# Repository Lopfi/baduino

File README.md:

# baduino
This is baduino!
An open source bad usb based on the Atmega 32u4. It is inspired by and uses the firmware from Seytonics Malduino Elite. 
It can store up to 16 different scripts on it's SD card, each of which can be selected on the fly with 4 dip switches.

# Firmware and bootloader
Get the firmware and arduino config from the malduino repository: [https://github.com/Seytonic/malduino](https://github.com/Seytonic/malduino)

# TODO
- Make PCB a bit nicer
- Create BOM
- Create Case
- Create own firmware with PIO
- Create proper documentation

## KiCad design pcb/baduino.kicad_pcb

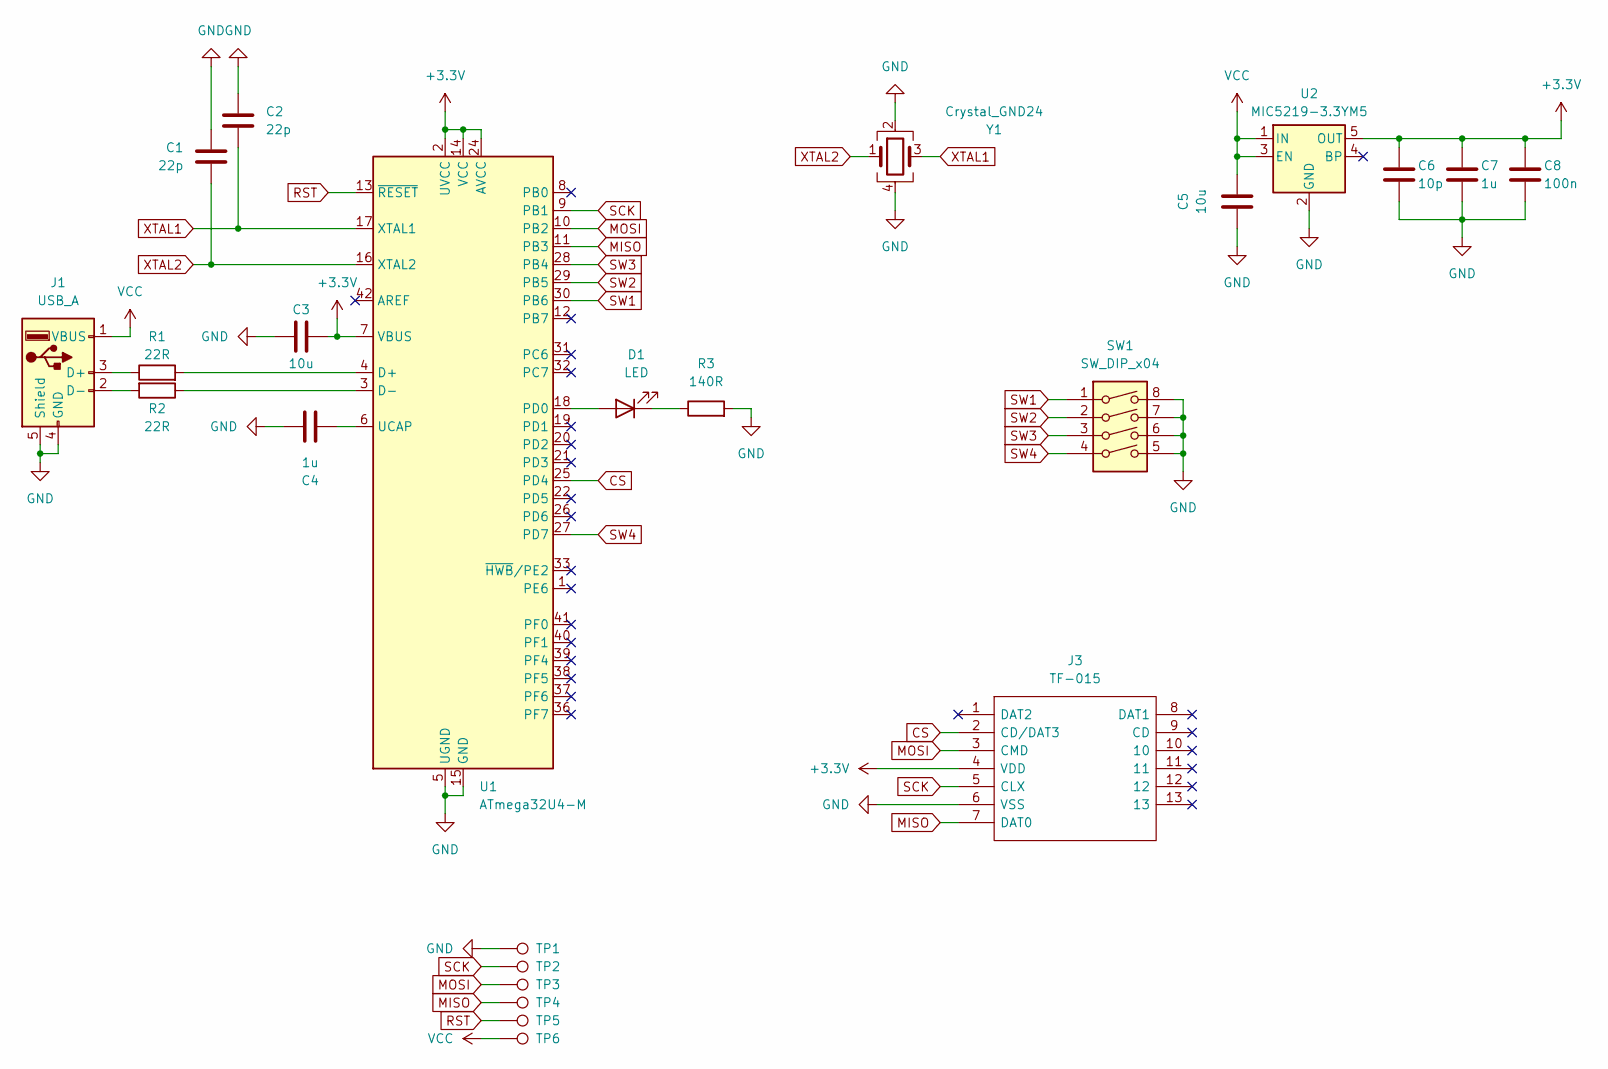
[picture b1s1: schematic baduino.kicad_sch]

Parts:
C1, C2: 22p; C_0805_2012Metric_Pad1.18x1.45mm_HandSolder
C3, C5: 10u; C_0805_2012Metric_Pad1.18x1.45mm_HandSolder
C4, C7: 1u; C_0805_2012Metric_Pad1.18x1.45mm_HandSolder
C6: 10p; C_0805_2012Metric_Pad1.18x1.45mm_HandSolder
C8: 100n; C_0805_2012Metric_Pad1.18x1.45mm_HandSolder
D1: LED; LED_0805_2012Metric_Pad1.15x1.40mm_HandSolder
J1: USB_A; USB_A_CNCTech_1001-011-01101_Horizontal
J3: TF-015; TF015; Manufacturer_Part_Number TF-015
R1, R2: 22R; R_0805_2012Metric_Pad1.20x1.40mm_HandSolder
R3: 140R; R_0805_2012Metric_Pad1.20x1.40mm_HandSolder
SW1: SW_DIP_x04; DIP-8_W7.62mm_SMDSocket_SmallPads
TP1, TP2, TP3, TP4, TP5, TP6: TestPoint; TestPoint_Pad_D1.0mm
U1: ATmega32U4-M; QFN-44-1EP_7x7mm_P0.5mm_EP5.2x5.2mm
U2: MIC5219-3.3YM5; SOT-23-5
Y1: Crystal_GND24; Crystal_SMD_3225-4Pin_3.2x2.5mm_HandSoldering

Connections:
+3.3V: C3.2, C6.1, C7.1, C8.1, J3.4 (VDD), U1.2 (UVCC), U1.7 (VBUS), U1.14 (VCC), U1.24 (AVCC), U1.34 (VCC), U1.44 (AVCC), U2.5 (OUT)
CS: J3.2 (CD/DAT3), U1.25 (PD4)
GND: C1.1, C2.1, C3.1, C4.1, C5.1, C6.2, C7.2, C8.2, J1.4 (GND), J1.5 (Shield), J3.6 (VSS), R3.2, SW1.5, SW1.6, SW1.7, SW1.8, TP1.1, U1.5 (UGND), U1.15 (GND), U1.23 (GND), U1.35 (GND), U1.43 (GND), U1.45 (GND), U2.2 (GND), Y1.2, Y1.4
MISO: J3.7 (DAT0), TP4.1, U1.11 (PB3)
MOSI: J3.3 (CMD), TP3.1, U1.10 (PB2)
unnamed: D1.2 (A), U1.18 (PD0)
unnamed: D1.1 (K), R3.1
unnamed: J1.3 (D+), R1.1
unnamed: J1.2 (D-), R2.2
unnamed: R1.2, U1.4 (D+)
unnamed: R2.1, U1.3 (D-)
unnamed: C4.2, U1.6 (UCAP)
RST: TP5.1, U1.13 (~RESET)
SCK: J3.5 (CLX), TP2.1, U1.9 (PB1)
SW1: SW1.1, U1.30 (PB6)
SW2: SW1.2, U1.29 (PB5)
SW3: SW1.3, U1.28 (PB4)
SW4: SW1.4, U1.27 (PD7)
VCC: C5.2, J1.1 (VBUS), TP6.1, U2.1 (IN), U2.3 (EN)
XTAL1: C2.2, U1.17 (XTAL1), Y1.3
XTAL2: C1.2, U1.16 (XTAL2), Y1.1

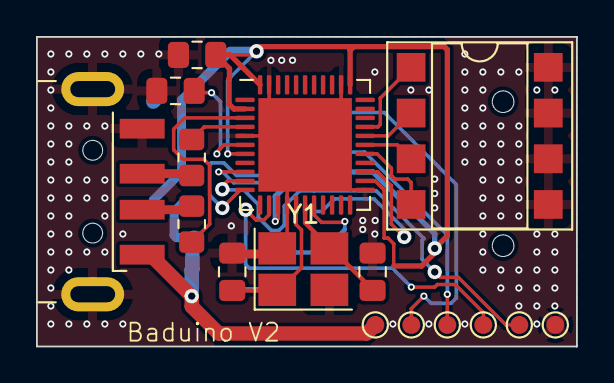
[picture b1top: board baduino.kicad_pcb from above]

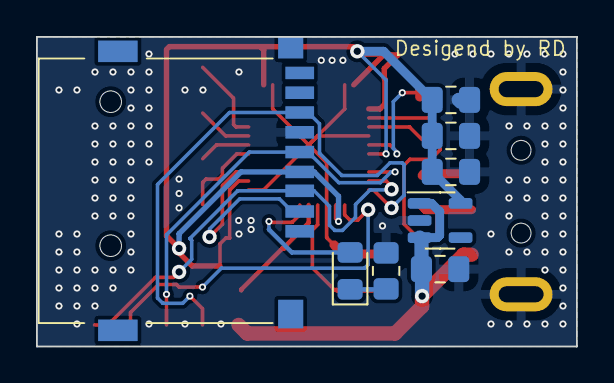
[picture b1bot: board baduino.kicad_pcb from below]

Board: 2 copper layers, 30.0 x 17.2 mm, 24 parts (8 on the bottom side), 21 nets.

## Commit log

2024-01-23 pcb version at first prod run
2024-01-23 switch to non powered crystal oscillator
